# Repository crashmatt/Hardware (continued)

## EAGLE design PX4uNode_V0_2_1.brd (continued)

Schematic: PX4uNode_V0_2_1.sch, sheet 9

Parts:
D901: DIODE-SCHOTTKY; SOD-523; PARTNO MBRA140
D902, D903: B340A; SMA-DIODE; PARTNO B340A
D904: MSS1P4-M3; MICROSMP; PARTNO MSS1P4-M3/89A
JP901: M02PTH3; 1X02_LONGPADS
R901, R902, R903: 10K/0.1%; 0402-RES; PARTNO ERA-2AEB103X

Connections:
GND: D901.A, JP901.2, R903.P$1 (1); also elsewhere on the board
unnamed: D901.C, R901.P$1 (1), R902.P$2 (2)
VBUS: D904.ANODE (A); also elsewhere on the board
VDD_IN: D902.C, D903.C, D904.CATHODE (C); also elsewhere on the board
VDD_SERVO_SENSE: R902.P$1 (1), R903.P$2 (2); also elsewhere on the board
V_EXT: D903.A, JP901.1, R901.P$2 (2)
V_SERVO: D902.A; also elsewhere on the board

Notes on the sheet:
IO SoC Ports Spektrum/DSM port
Timer allocation: PA0: TIM2_CH1: IO-CH1 PA1: TIM2_CH2: IO-CH2 PB8: TIM4_CH3: IO-CH3 PB9: TIM4_CH4: IO-CH4 PA6: TIM3_CH1: IO-CH5 PA7: TIM3_CH2: IO-CH6 PB0: TIM3_CH3: IO-CH7 PB1: TIM3_CH4: IO-CH8 PA8: TIM1_CH1: PPM_IN PA11: TIM1_CH4: RSSI_IN

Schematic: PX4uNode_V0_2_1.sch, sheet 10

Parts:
J1001: SERVO_HEADER-3X8; 3X8RA_SERVO
JP1001, JP1002: M01SMD-4.5X1.5; PAD-1.5X4.5
L1001: NUF8402MN; DFN16-THIN; PARTNO NUF8402MN
R1001, R1002: 220R; 0402-RES; PARTNO RC0402FR-07220RL

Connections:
FMU-CH1: L1001.P$4; also elsewhere on the board
FMU-CH1-PROT: J1001.S1, L1001.P$9
FMU-CH2: L1001.P$5; also elsewhere on the board
FMU-CH3: L1001.P$6; also elsewhere on the board
FMU-CH4: L1001.P$7; also elsewhere on the board
FMU-CH5: L1001.P$2; also elsewhere on the board
FMU-CH6: L1001.P$3; also elsewhere on the board
FMU-CH7: L1001.P$8; also elsewhere on the board
FMU-CH8: L1001.P$1; also elsewhere on the board
FMU-CH9: R1001.P$2 (2); also elsewhere on the board
FMU-CH10: R1002.P$2 (2); also elsewhere on the board
GND: J1001.GND_S1, J1001.GND_S2, J1001.GND_S3, J1001.GND_S4, J1001.GND_S5, J1001.GND_S6, J1001.GND_S7, J1001.GND_S8, L1001.P$EP (GND); also elsewhere on the board
unnamed: J1001.S8, L1001.P$16
unnamed: J1001.S7, L1001.P$15
unnamed: JP1001.P$1, R1001.P$1 (1)
unnamed: JP1002.P$1, R1002.P$1 (1)
unnamed: J1001.S6, L1001.P$14
unnamed: J1001.S5, L1001.P$13
unnamed: J1001.S4, L1001.P$11
unnamed: J1001.S3, L1001.P$12
unnamed: J1001.S2, L1001.P$10
V_SERVO: J1001.PWR_S1, J1001.PWR_S2, J1001.PWR_S3, J1001.PWR_S4, J1001.PWR_S5, J1001.PWR_S6, J1001.PWR_S7, J1001.PWR_S8; also elsewhere on the board

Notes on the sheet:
Servo Header S.Bus interface
Servo outputs

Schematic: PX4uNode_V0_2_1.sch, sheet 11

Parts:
JP1101, JP1102, JP1103, JP1104: FIDUCIAL1.5X3; FIDUCIAL-1.5X3; PARTNO *
JP1105: M01PTH; 1X01
M3_MOUNT1101, M3_MOUNT1102, M3_MOUNT1103, M3_MOUNT1104: MOUNT-HOLE3.1MM; MOUNT-HOLE3.1; PARTNO *
OSHW_LOGO: OSHW-LOGOS; OSHW-LOGO-S; PARTNO *

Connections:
FMU-BOOT0: JP1105.1; also elsewhere on the board

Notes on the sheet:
Mounting holes to suit M3 fastener
and Richco R908 series spacer.
Use R908-5 spacers to stack with
other PX4 series boards (7.95 mm).
Production Testing Pads
Test and Fiducials
Minimum drill: 0.3 mm
Minimum trace width (use mm for traces): 0.15 mm
Minimum copper distance (all signals): 0.15 mm
Dimension / hole minimum distance: 0.2 mm
Layout grid: 4 mil, part grid: 4 mil. Dimensions / hole positions: 0.5 mm
Board: FR4 black, 1.0 mm. Solder stop on vias < 0.6 mm.
Signoff rules: Footprint checked, pinmap checked, schematic checked, cross-references to other pages checked.
Routing: 1: general/escape 2: ground 3: horizontal 4: vertical 5: power 6: general/escape
Fiducials for machine vision alignment.

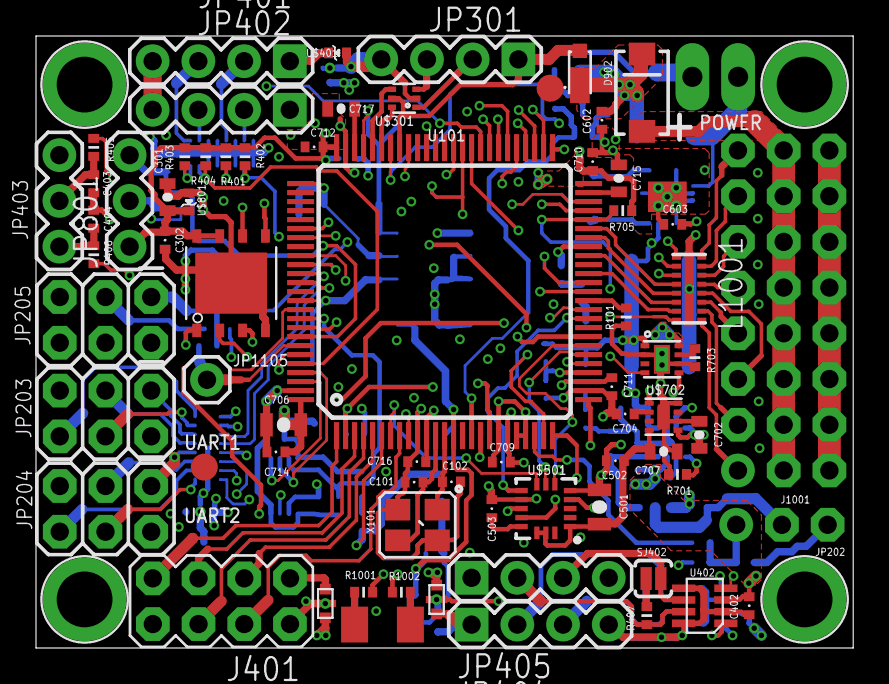
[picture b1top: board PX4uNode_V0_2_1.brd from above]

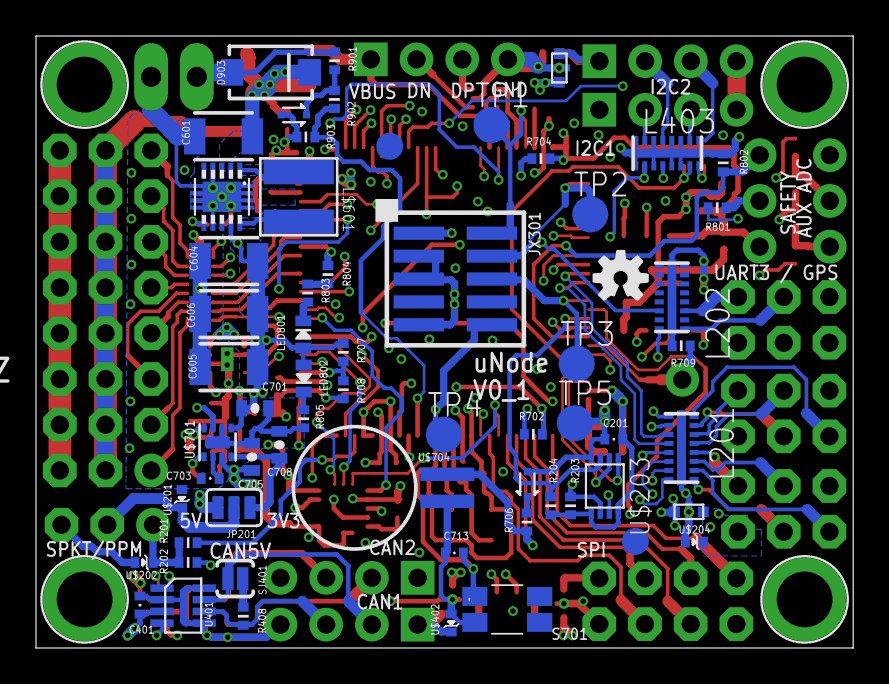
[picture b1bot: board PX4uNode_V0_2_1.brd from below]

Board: 6 copper layers, 45.4 x 34.0 mm, 138 parts (62 on the bottom side), 136 nets.

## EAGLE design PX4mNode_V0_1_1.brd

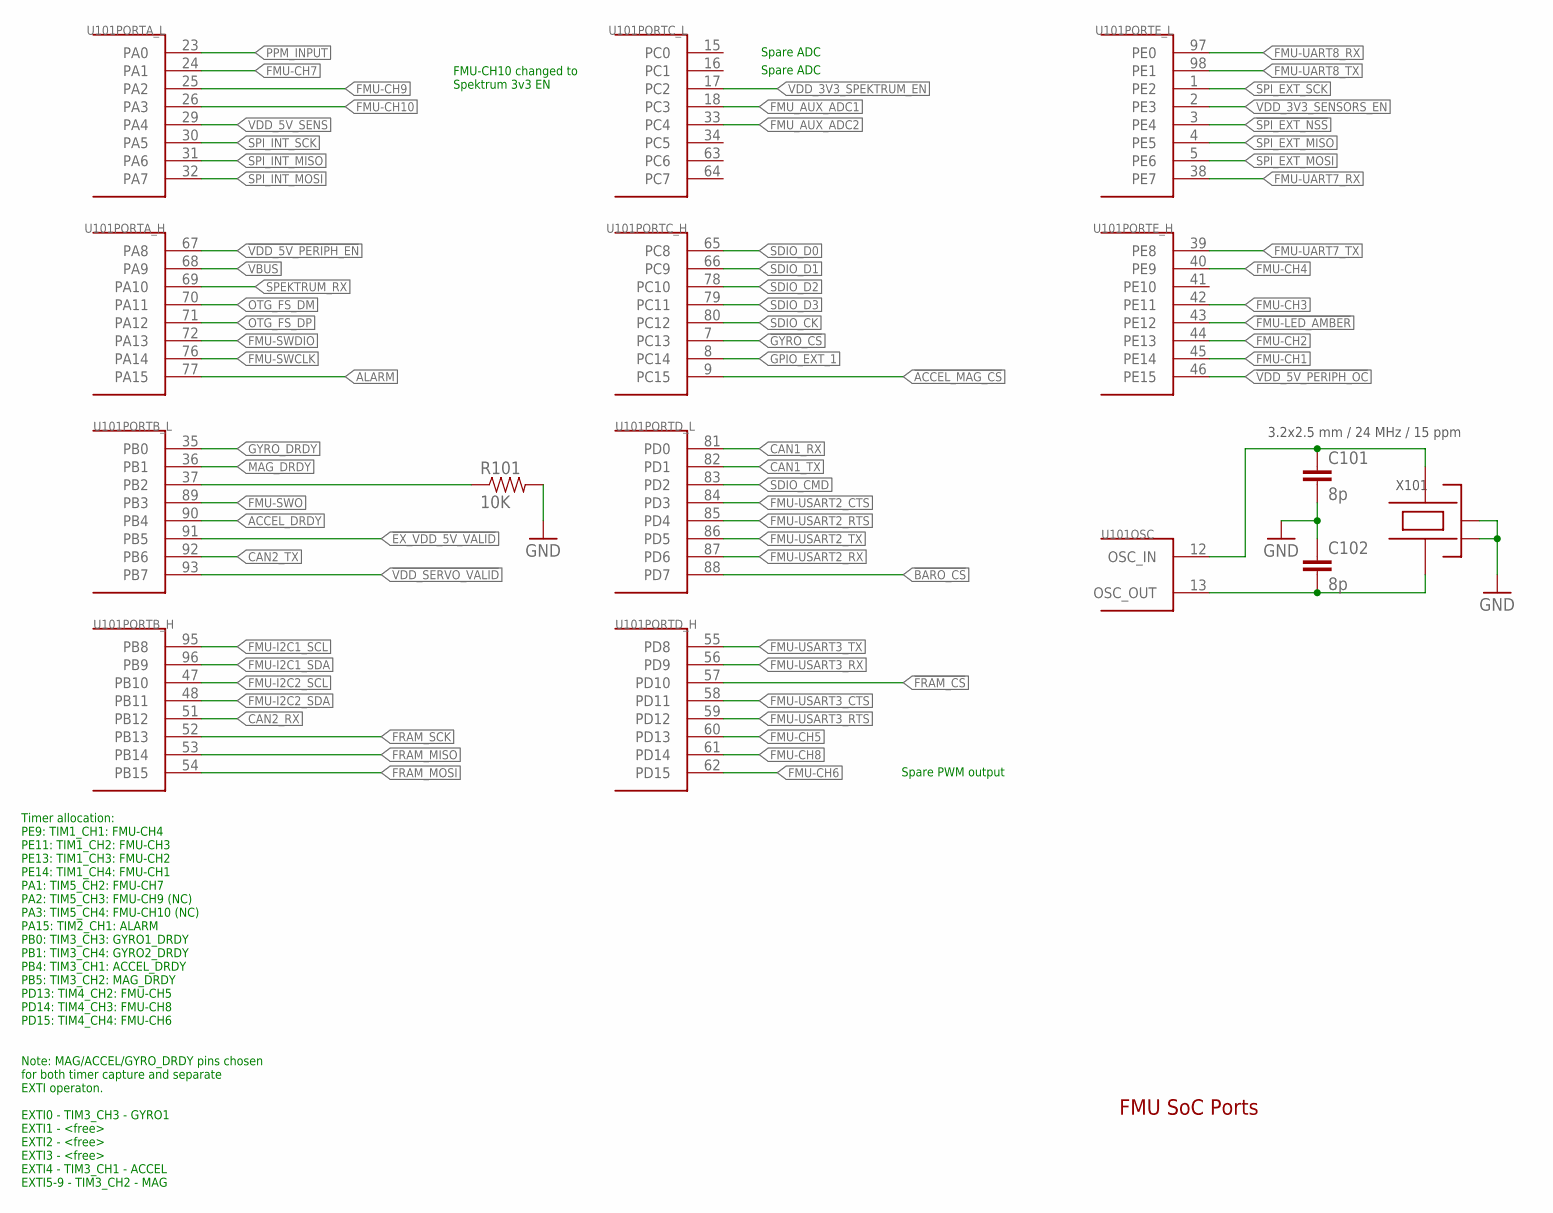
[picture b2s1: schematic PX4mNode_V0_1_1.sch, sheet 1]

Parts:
C101, C102: 8p; 0402-CAP; PARTNO C1005C0G1H080C
R101: 10K; 0402-RES; PARTNO RC0402FR-0710KL
U101: STM32F4X7VX; TQFP100; PARTNO STM32F427VI
X101: 3.2x2.5 mm / 24 MHz / 15 ppm; OSCILLATOR-3.2X2.5; PARTNO NX3225SA-24.000000MHZ

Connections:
!ACCEL_MAG_CS: U101.9 (PC15)
!BARO_CS: U101.88 (PD7)
!EX_VDD_5V_VALID: U101.91 (PB5)
!FMU-LED_AMBER: U101.43 (PE12); also elsewhere on the board
!FRAM_CS: U101.57 (PD10)
!GYRO_CS: U101.7 (PC13); also elsewhere on the board
!SPI_EXT_NSS: U101.3 (PE4); also elsewhere on the board
!VDD_5V_PERIPH_EN: U101.67 (PA8); also elsewhere on the board
!VDD_5V_PERIPH_OC: U101.46 (PE15); also elsewhere on the board
!VDD_SERVO_VALID: U101.93 (PB7)
ACCEL_DRDY: U101.90 (PB4); also elsewhere on the board
ALARM: U101.77 (PA15)
CAN1_RX: U101.81 (PD0); also elsewhere on the board
CAN1_TX: U101.82 (PD1); also elsewhere on the board
CAN2_RX: U101.51 (PB12); also elsewhere on the board
CAN2_TX: U101.92 (PB6); also elsewhere on the board
FMU-CH1: U101.45 (PE14); also elsewhere on the board
FMU-CH2: U101.44 (PE13); also elsewhere on the board
FMU-CH3: U101.42 (PE11); also elsewhere on the board
FMU-CH4: U101.40 (PE9); also elsewhere on the board
FMU-CH5: U101.60 (PD13); also elsewhere on the board
FMU-CH6: U101.62 (PD15); also elsewhere on the board
FMU-CH7: U101.24 (PA1); also elsewhere on the board
FMU-CH8: U101.61 (PD14); also elsewhere on the board
FMU-CH9: U101.25 (PA2); also elsewhere on the board
FMU-CH10: U101.26 (PA3); also elsewhere on the board
FMU-I2C1_SCL: U101.95 (PB8); also elsewhere on the board
FMU-I2C1_SDA: U101.96 (PB9); also elsewhere on the board
FMU-I2C2_SCL: U101.47 (PB10); also elsewhere on the board
FMU-I2C2_SDA: U101.48 (PB11); also elsewhere on the board
FMU-SWCLK: U101.76 (PA14); also elsewhere on the board
FMU-SWDIO: U101.72 (PA13); also elsewhere on the board
FMU-SWO: U101.89 (PB3); also elsewhere on the board
FMU-UART7_RX: U101.38 (PE7); also elsewhere on the board
FMU-UART7_TX: U101.39 (PE8); also elsewhere on the board
FMU-UART8_RX: U101.97 (PE0); also elsewhere on the board
FMU-UART8_TX: U101.98 (PE1); also elsewhere on the board
FMU-USART2_CTS: U101.84 (PD3); also elsewhere on the board
FMU-USART2_RTS: U101.85 (PD4); also elsewhere on the board
FMU-USART2_RX: U101.87 (PD6); also elsewhere on the board
FMU-USART2_TX: U101.86 (PD5); also elsewhere on the board
FMU-USART3_CTS: U101.58 (PD11); also elsewhere on the board
FMU-USART3_RTS: U101.59 (PD12); also elsewhere on the board
FMU-USART3_RX: U101.56 (PD9); also elsewhere on the board
FMU-USART3_TX: U101.55 (PD8); also elsewhere on the board
FMU_AUX_ADC1: U101.18 (PC3); also elsewhere on the board
FMU_AUX_ADC2: U101.33 (PC4); also elsewhere on the board
FRAM_MISO: U101.53 (PB14)
FRAM_MOSI: U101.54 (PB15)
FRAM_SCK: U101.52 (PB13)
GND: C101.P$2 (2), C102.P$1 (1), R101.P$2 (2), X101.2 (NC_2), X101.4 (NC_4); also elsewhere on the board
GPIO_EXT_1: U101.8 (PC14); also elsewhere on the board
GYRO_DRDY: U101.35 (PB0); also elsewhere on the board
MAG_DRDY: U101.36 (PB1); also elsewhere on the board
unnamed: C102.P$2 (2), U101.13 (OSC_OUT), X101.1
unnamed: C101.P$1 (1), U101.12 (OSC_IN), X101.3
OTG_FS_DM: U101.70 (PA11); also elsewhere on the board
OTG_FS_DP: U101.71 (PA12); also elsewhere on the board
PB2-BOOT1: R101.P$1 (1), U101.37 (PB2)
PPM_INPUT: U101.23 (PA0); also elsewhere on the board
SDIO_CK: U101.80 (PC12); also elsewhere on the board
SDIO_CMD: U101.83 (PD2); also elsewhere on the board
SDIO_D0: U101.65 (PC8); also elsewhere on the board
SDIO_D1: U101.66 (PC9); also elsewhere on the board
SDIO_D2: U101.78 (PC10); also elsewhere on the board
SDIO_D3: U101.79 (PC11); also elsewhere on the board
SPEKTRUM_RX: U101.69 (PA10); also elsewhere on the board
SPI_EXT_MISO: U101.4 (PE5); also elsewhere on the board
SPI_EXT_MOSI: U101.5 (PE6); also elsewhere on the board
SPI_EXT_SCK: U101.1 (PE2); also elsewhere on the board
SPI_INT_MISO: U101.31 (PA6); also elsewhere on the board
SPI_INT_MOSI: U101.32 (PA7); also elsewhere on the board
SPI_INT_SCK: U101.30 (PA5); also elsewhere on the board
VBUS: U101.68 (PA9); also elsewhere on the board
VDD_3V3_SENSORS_EN: U101.2 (PE3); also elsewhere on the board
VDD_3V3_SPEKTRUM_EN: U101.17 (PC2); also elsewhere on the board
VDD_5V_SENS: U101.29 (PA4); also elsewhere on the board

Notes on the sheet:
FMU SoC Ports
Note: MAG/ACCEL/GYRO_DRDY pins chosen for both timer capture and separate EXTI operaton. EXTI0 - TIM3_CH3 - GYRO1 EXTI1 - <free> EXTI2 - <free> EXTI3 - <free> EXTI4 - TIM3_CH1 - ACCEL EXTI5-9 - TIM3_CH2 - MAG
Timer allocation: PE9: TIM1_CH1: FMU-CH4 PE11: TIM1_CH2: FMU-CH3 PE13: TIM1_CH3: FMU-CH2 PE14: TIM1_CH4: FMU-CH1 PA1: TIM5_CH2: FMU-CH7 PA2: TIM5_CH3: FMU-CH9 (NC) PA3: TIM5_CH4: FMU-CH10 (NC) PA15: TIM2_CH1: ALARM PB0: TIM3_CH3: GYRO1_DRDY PB1: TIM3_CH4: GYRO2_DRDY PB4: TIM3_CH1: ACCEL_DRDY PB5: T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
Spare PWM output
Spare ADC
FMU-CH10 changed to Spektrum 3v3 EN

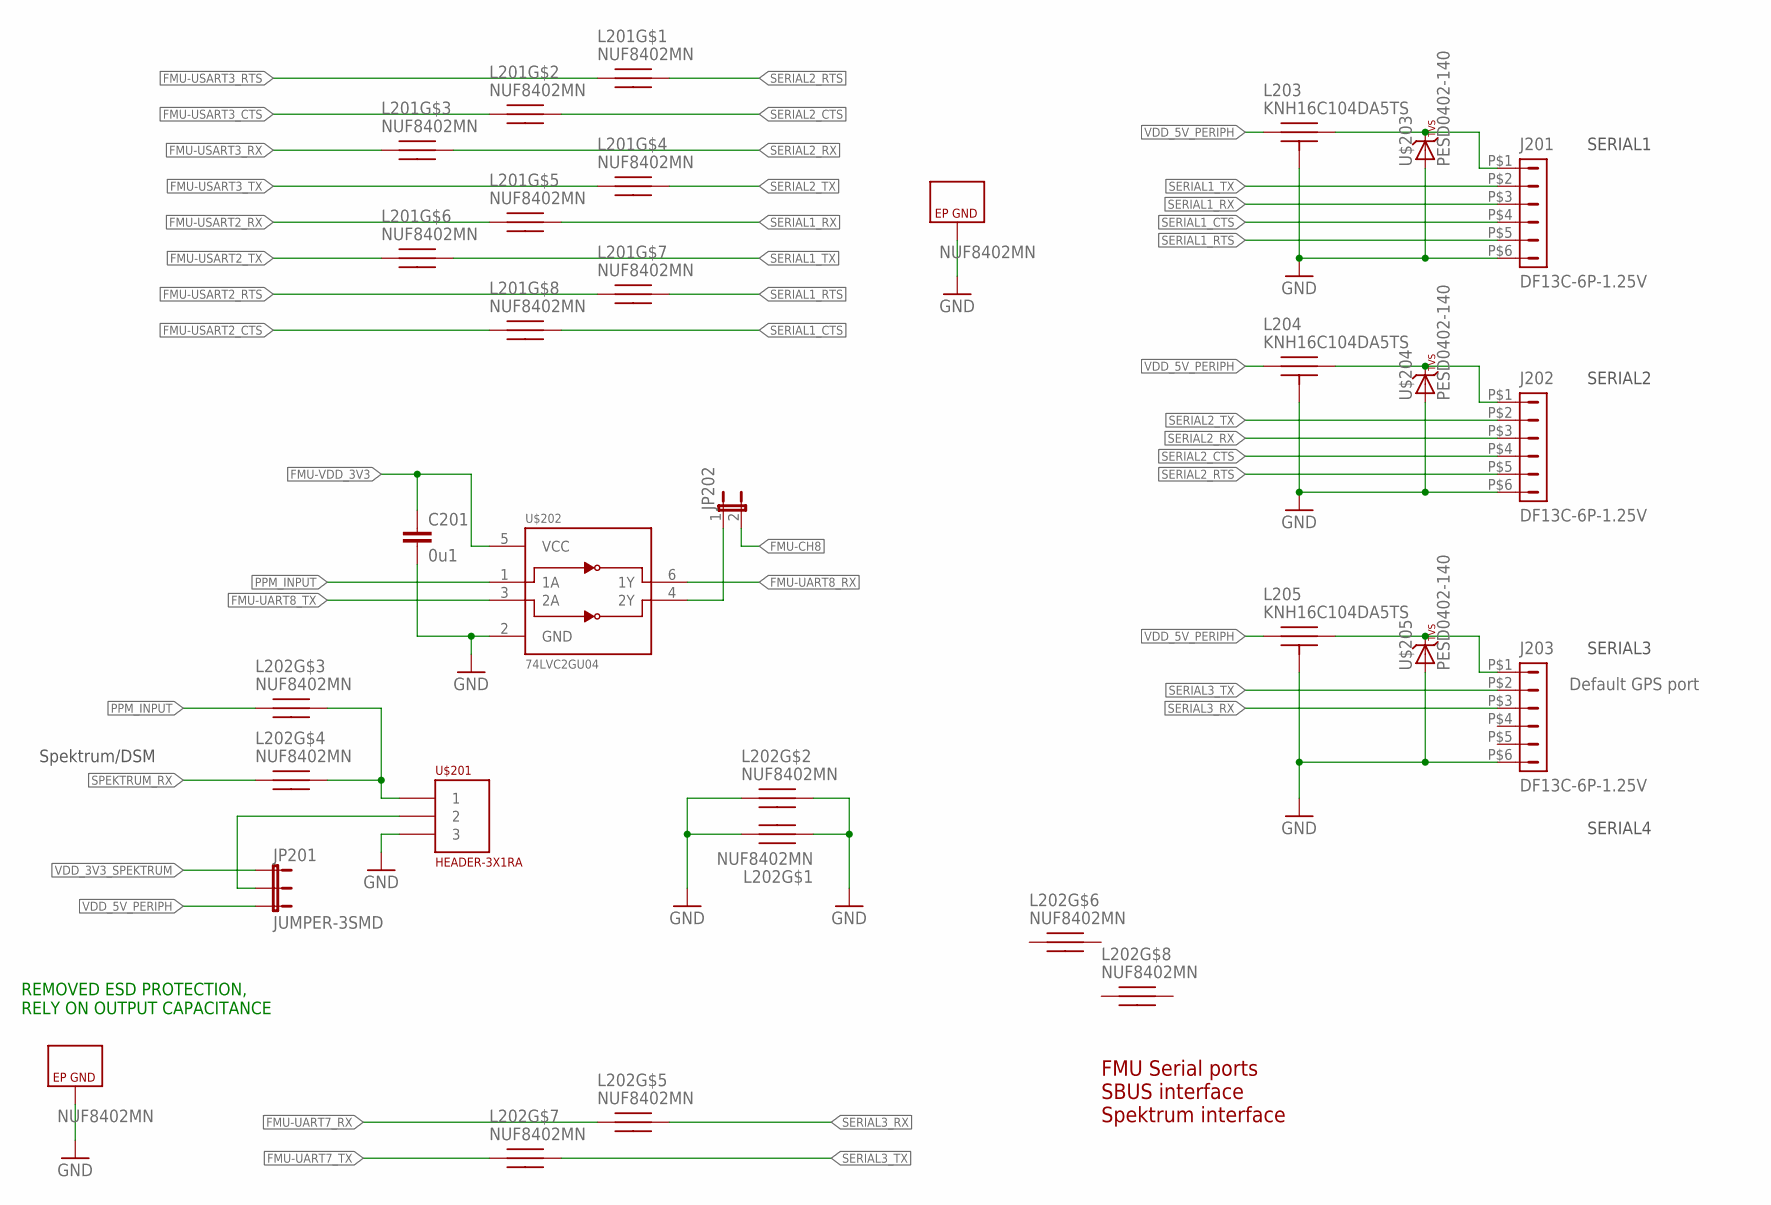
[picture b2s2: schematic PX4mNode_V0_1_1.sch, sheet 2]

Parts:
C201: 0u1; 0402-CAP; PARTNO CC0402ZRY5V7BB104
J201, J202, J203: DF13C-6P-1.25V; PARTNO DF13C-6P-1.25V(20)
JP201: JUMPER-3SMD; SJ_3
JP202: JUMPER-2SMD-NO; SJ_2S-NO
L201, L202: NUF8402MN; DFN16-THIN
L203, L204, L205: KNH16C104DA5TS; KYOCERA-KNH16-DA; PARTNO KNH16C104DA5TS
U$201: HEADER-3X1RA; 3X1RA
U$202: 74LVC2GU04; SOT363_PHILIPS; PARTNO 74LVC2GU04
U$203, U$204, U$205: PESD0402-140; 0402-TVS; PARTNO PESD0402-140

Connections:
5V_S1_FILTERED: J201.P$1 (1), L203.P$2, U$203.C
5V_S2_FILTERED: J202.P$1 (1), L204.P$2, U$204.C
5V_S3_FILTERED: J203.P$1 (1), L205.P$2, U$205.C
FMU-CH8: JP202.2; also elsewhere on the board
FMU-UART7_RX: L202.P$5; also elsewhere on the board
FMU-UART7_TX: L202.P$7; also elsewhere on the board
FMU-UART8_RX: U$202.6 (1Y); also elsewhere on the board
FMU-UART8_TX: U$202.3 (2A); also elsewhere on the board
FMU-USART2_CTS: L201.P$8; also elsewhere on the board
FMU-USART2_RTS: L201.P$7; also elsewhere on the board
FMU-USART2_RX: L201.P$5; also elsewhere on the board
FMU-USART2_TX: L201.P$6; also elsewhere on the board
FMU-USART3_CTS: L201.P$2; also elsewhere on the board
FMU-USART3_RTS: L201.P$1; also elsewhere on the board
FMU-USART3_RX: L201.P$3; also elsewhere on the board
FMU-USART3_TX: L201.P$4; also elsewhere on the board
FMU-VDD_3V3: C201.P$1 (1), U$202.5 (VCC); also elsewhere on the board
GND: C201.P$2 (2), J201.P$6 (6), J202.P$6 (6), J203.P$6 (6), L201.P$EP (GND), L202.P$1, L202.P$2, L202.P$15, L202.P$16, L202.P$EP (GND), L203.P$3, L203.P$4, L203.P$5, L204.P$3, L204.P$4, L204.P$5, L205.P$3, L205.P$4, L205.P$5, U$201.3, U$202.2 (GND), U$203.A, U$204.A, U$205.A; also elsewhere on the board
unnamed: JP202.1, U$202.4 (2Y)
unnamed: L202.P$13, L202.P$14, U$201.1
PPM_INPUT: L202.P$3, U$202.1 (1A); also elsewhere on the board
SERIAL1_CTS: J201.P$4 (4), L201.P$9
SERIAL1_RTS: J201.P$5 (5), L201.P$10
SERIAL1_RX: J201.P$3 (3), L201.P$12
SERIAL1_TX: J201.P$2 (2), L201.P$11
SERIAL2_CTS: J202.P$4 (4), L201.P$15
SERIAL2_RTS: J202.P$5 (5), L201.P$16
SERIAL2_RX: J202.P$3 (3), L201.P$14
SERIAL2_TX: J202.P$2 (2), L201.P$13
SERIAL3_RX: J203.P$3 (3), L202.P$12
SERIAL3_TX: J203.P$2 (2), L202.P$10
SPEKTRUM_RX: L202.P$4; also elsewhere on the board
VDD_3V3_SPEKTRUM: JP201.1; also elsewhere on the board
VDD_5V_PERIPH: JP201.3, L203.P$1, L204.P$1, L205.P$1; also elsewhere on the board
VDD_RX_POWER: JP201.2, U$201.2

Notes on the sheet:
FMU Serial ports SBUS interface Spektrum interface
SERIAL2
SERIAL1
SERIAL3
SERIAL4
Default GPS port
Spektrum/DSM
REMOVED ESD PROTECTION, RELY ON OUTPUT CAPACITANCE

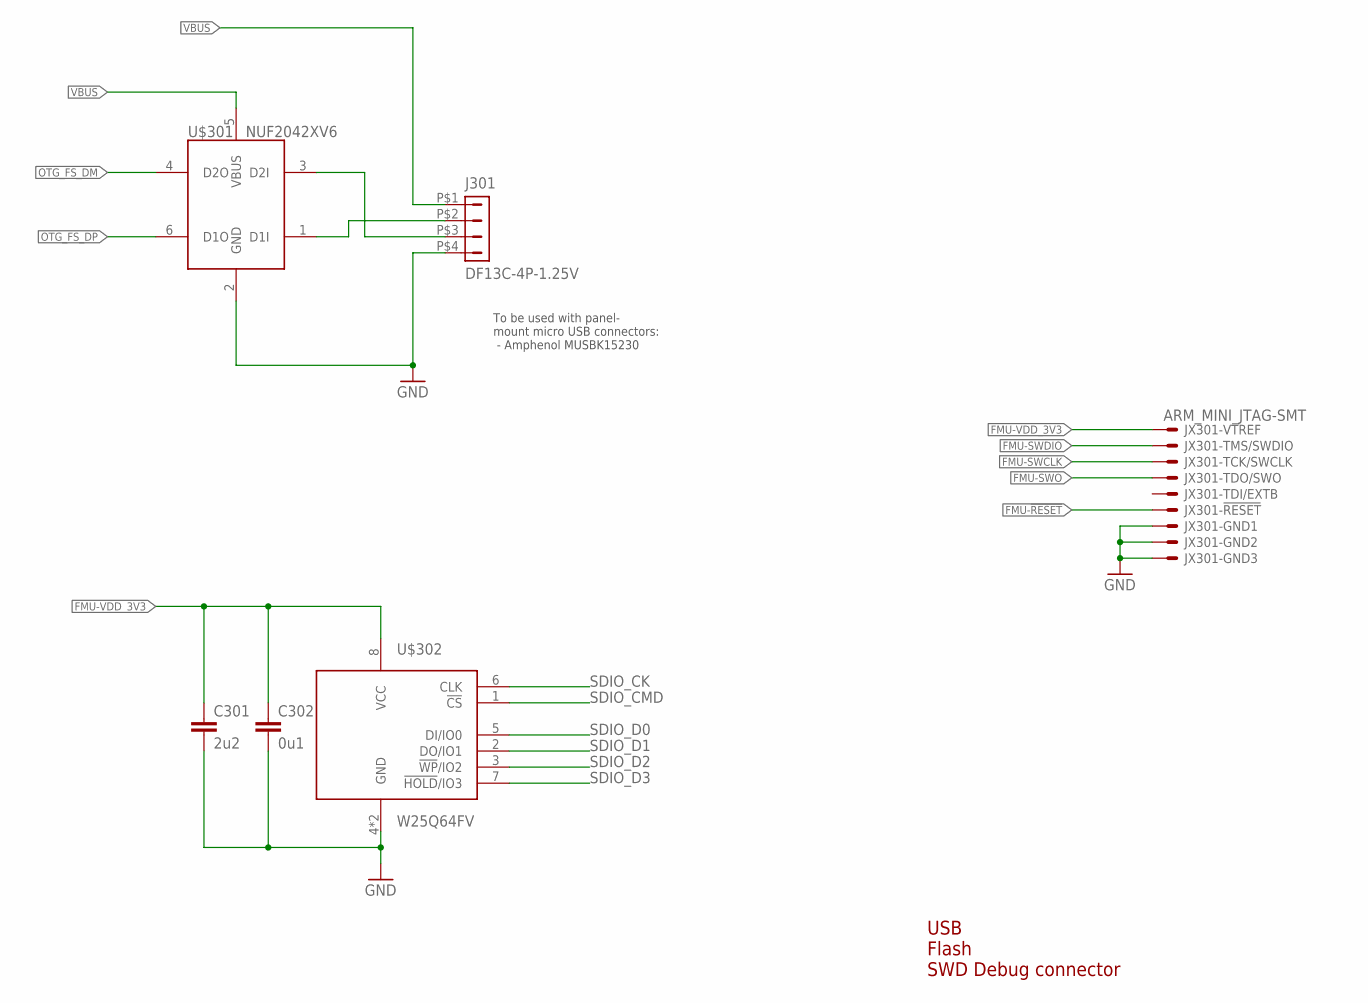
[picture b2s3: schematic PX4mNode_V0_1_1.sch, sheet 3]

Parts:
C301: 2u2; 0603-CAP; PARTNO C1608Y5V1C225Z
C302: 0u1; 0402-CAP; PARTNO CC0402ZRY5V7BB104
J301: DF13C-4P-1.25V; PARTNO DF13C-4P-1.25V(20)
JX301: ARM_MINI_JTAG-SMT; FTSH-105-01-XXX-DV-K; PARTNO M50-3900542
U$301: NUF2042XV6; SOT563-6
U$302: W25Q64FV; WSON-8-5X6

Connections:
FMU-!RESET: JX301.10; also elsewhere on the board
FMU-SWCLK: JX301.4; also elsewhere on the board
FMU-SWDIO: JX301.2; also elsewhere on the board
FMU-SWO: JX301.6; also elsewhere on the board
FMU-VDD_3V3: C301.P$1 (1), C302.P$1 (1), JX301.1, U$302.8 (VCC); also elsewhere on the board
GND: C301.P$2 (2), C302.P$2 (2), J301.P$4 (4), JX301.3, JX301.5, JX301.9, U$301.2 (GND), U$302.4 (GND), U$302.PAD (GND); also elsewhere on the board
OTG_DM1: J301.P$3 (3), U$301.3 (D2I)
OTG_DP1: J301.P$2 (2), U$301.1 (D1I)
OTG_FS_DM: U$301.4 (D2O); also elsewhere on the board
OTG_FS_DP: U$301.6 (D1O); also elsewhere on the board
SDIO_CK: U$302.6 (CLK); also elsewhere on the board
SDIO_CMD: U$302.1 (!CS); also elsewhere on the board
SDIO_D0: U$302.5 (DI/IO0); also elsewhere on the board
SDIO_D1: U$302.2 (DO/IO1); also elsewhere on the board
SDIO_D2: U$302.3 (!WP!/IO2); also elsewhere on the board
SDIO_D3: U$302.7 (!HOLD!/IO3); also elsewhere on the board
VBUS: J301.P$1 (1), U$301.5 (VBUS); also elsewhere on the board

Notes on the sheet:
USB Flash SWD Debug connector
To be used with panel- mount micro USB connectors: - Amphenol MUSBK15230

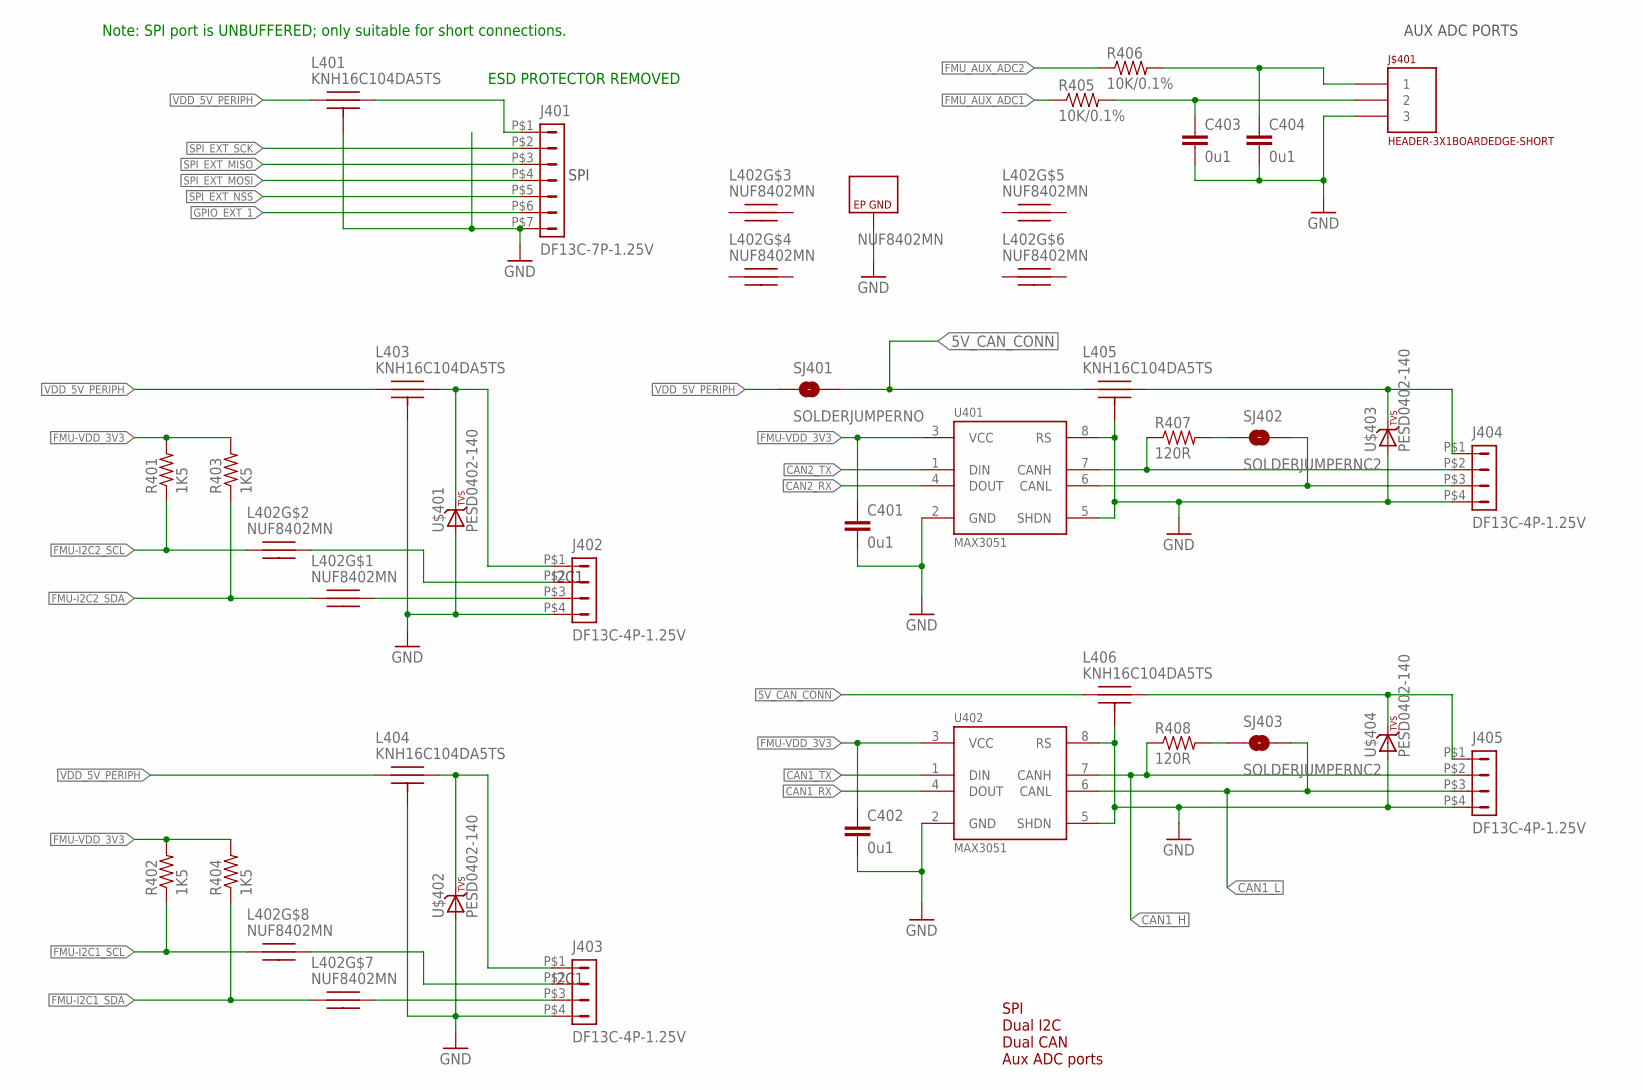
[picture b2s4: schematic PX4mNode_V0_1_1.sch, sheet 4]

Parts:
C401, C402, C403, C404: 0u1; 0402-CAP; PARTNO CC0402ZRY5V7BB104
J401: DF13C-7P-1.25V; PARTNO DF13C-7P-1.25V(20)
J402, J403, J404, J405: DF13C-4P-1.25V; PARTNO DF13C-4P-1.25V(20)
J$401: HEADER-3X1BOARDEDGE-SHORT; HEADER_3X01_SMD_H_BOARD_EDGE_SHORT
L401, L403, L404, L405, L406: KNH16C104DA5TS; KYOCERA-KNH16-DA; PARTNO KNH16C104DA5TS
L402: NUF8402MN; DFN16-THIN
R401, R402, R403, R404: 1K5; 0402-RES; PARTNO RC0402FR-071K5L
R405, R406: 10K/0.1%; 0402-RES; PARTNO ERA-2AEB103X
R407, R408: 120R; 0402-RES; PARTNO RC0402FR-07120RL
SJ401: SOLDERJUMPERNO; SJ_2S-NO
SJ402, SJ403: SOLDERJUMPERNC2; SJ_2S-NOTRACE
U401, U402: MAX3051; SOT23-8; PARTNO MAX3051EKA
U$401, U$402, U$403, U$404: PESD0402-140; 0402-TVS; PARTNO PESD0402-140

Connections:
5V_CAN_CONN: L405.P$1, L406.P$1, SJ401.2
!SPI_EXT_NSS: J401.P$5 (5); also elsewhere on the board
CAN1_H: J405.P$2 (2), R408.P$1 (1), U402.7 (CANH)
CAN1_L: J405.P$3 (3), SJ403.2, U402.6 (CANL)
CAN1_RX: U402.4 (DOUT); also elsewhere on the board
CAN1_TX: U402.1 (DIN); also elsewhere on the board
CAN2_H: J404.P$2 (2), R407.P$1 (1), U401.7 (CANH)
CAN2_L: J404.P$3 (3), SJ402.2, U401.6 (CANL)
CAN2_RX: U401.4 (DOUT); also elsewhere on the board
CAN2_TX: U401.1 (DIN); also elsewhere on the board
FMU-I2C1_SCL: L402.P$8, R402.P$1 (1); also elsewhere on the board
FMU-I2C1_SDA: L402.P$7, R404.P$1 (1); also elsewhere on the board
FMU-I2C2_SCL: L402.P$2, R401.P$1 (1); also elsewhere on the board
FMU-I2C2_SDA: L402.P$1, R403.P$1 (1); also elsewhere on the board
FMU-VDD_3V3: C401.P$1 (1), C402.P$1 (1), R401.P$2 (2), R402.P$2 (2), R403.P$2 (2), R404.P$2 (2), U401.3 (VCC), U402.3 (VCC); also elsewhere on the board
FMU_AUX_ADC1: R405.P$1 (1); also elsewhere on the board
FMU_AUX_ADC1_PROT: C403.P$1 (1), J$401.2, R405.P$2 (2)
FMU_AUX_ADC2: R406.P$1 (1); also elsewhere on the board
FMU_AUX_ADC2_PROT: C404.P$1 (1), J$401.1, R406.P$2 (2)
GND: C401.P$2 (2), C402.P$2 (2), C403.P$2 (2), C404.P$2 (2), J401.P$7 (7), J402.P$4 (4), J403.P$4 (4), J404.P$4 (4), J405.P$4 (4), J$401.3, L401.P$3, L401.P$4, L401.P$5, L402.P$EP (GND), L403.P$3, L403.P$4, L403.P$5, L404.P$3, L404.P$4, L404.P$5, L405.P$3, L405.P$4, L405.P$5, L406.P$3, L406.P$4, L406.P$5, U401.2 (GND), U401.5 (SHDN), U401.8 (RS), U402.2 (GND), U402.5 (SHDN), U402.8 (RS), U$401.A, U$402.A, U$403.A, U$404.A; also elsewhere on the board
GPIO_EXT_1: J401.P$6 (6); also elsewhere on the board
unnamed: J402.P$2 (2), L402.P$15
unnamed: J402.P$3 (3), L402.P$16
unnamed: J402.P$1 (1), L403.P$2, U$401.C
unnamed: R408.P$2 (2), SJ403.1
unnamed: J404.P$1 (1), L405.P$2, U$403.C
unnamed: R407.P$2 (2), SJ402.1
unnamed: J403.P$2 (2), L402.P$9
unnamed: J403.P$3 (3), L402.P$10
unnamed: J401.P$1 (1), L401.P$2
unnamed: J403.P$1 (1), L404.P$2, U$402.C
unnamed: J405.P$1 (1), L406.P$2, U$404.C
SPI_EXT_MISO: J401.P$3 (3); also elsewhere on the board
SPI_EXT_MOSI: J401.P$4 (4); also elsewhere on the board
SPI_EXT_SCK: J401.P$2 (2); also elsewhere on the board
VDD_5V_PERIPH: L401.P$1, L403.P$1, L404.P$1, SJ401.1; also elsewhere on the board

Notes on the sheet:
SPI
I2C1
AUX ADC PORTS
SPI Dual I2C Dual CAN Aux ADC ports
Note: SPI port is UNBUFFERED; only suitable for short connections.
ESD PROTECTOR REMOVED

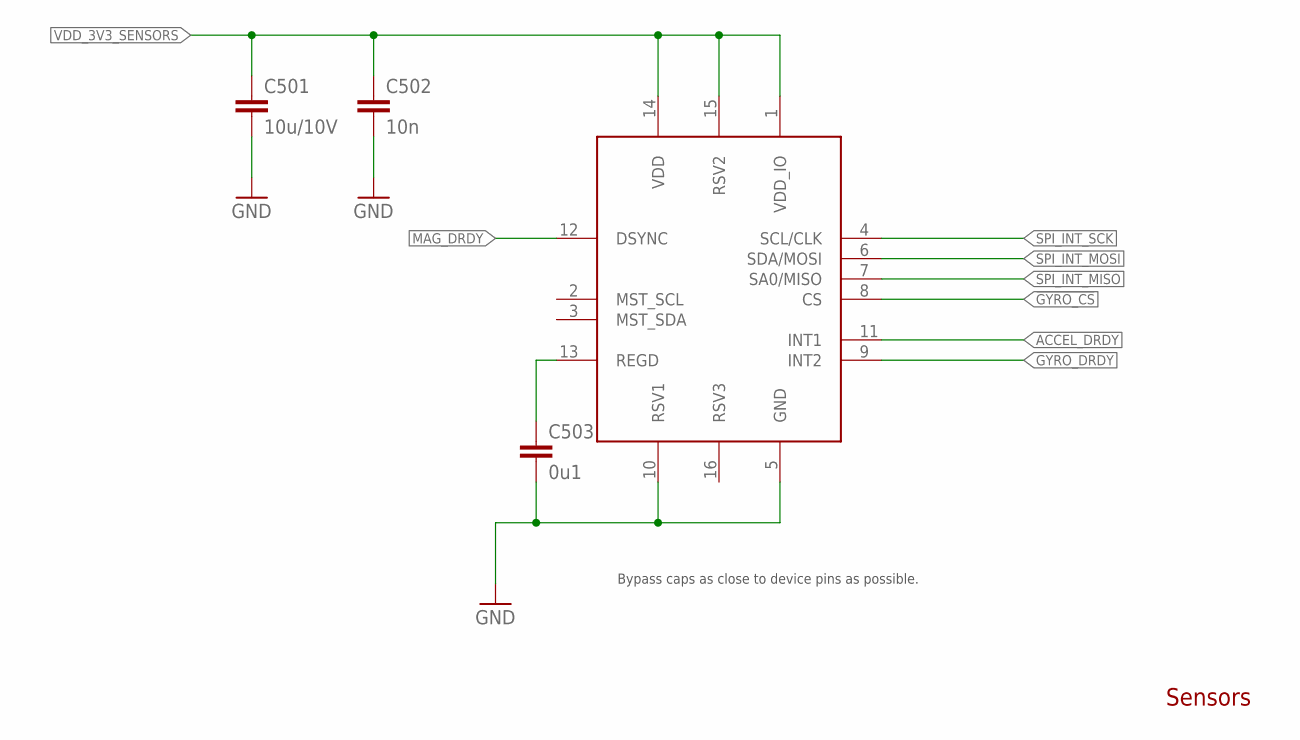
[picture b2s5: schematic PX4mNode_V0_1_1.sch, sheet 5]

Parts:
C501: 10u/10V; 0805-CAP; PARTNO CC0805ZKY5V6BB106
C502: 10n; 0402-CAP; PARTNO CC0402KRX7R7BB103
C503: 0u1; 0402-CAP; PARTNO CC0402ZRY5V7BB104
U$501: MAX21100; 16LGA-3X3

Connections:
!GYRO_CS: U$501.8 (CS); also elsewhere on the board
ACCEL_DRDY: U$501.11 (INT1); also elsewhere on the board
GND: C501.P$2 (2), C502.P$2 (2), C503.P$2 (2), U$501.5 (GND), U$501.10 (RSV1); also elsewhere on the board
GYRO_DRDY: U$501.9 (INT2); also elsewhere on the board
MAG_DRDY: U$501.12 (DSYNC); also elsewhere on the board
REGD: C503.P$1 (1), U$501.13 (REGD)
SPI_INT_MISO: U$501.7 (SA0/MISO); also elsewhere on the board
SPI_INT_MOSI: U$501.6 (SDA/MOSI); also elsewhere on the board
SPI_INT_SCK: U$501.4 (SCL/CLK); also elsewhere on the board
VDD_3V3_SENSORS: C501.P$1 (1), C502.P$1 (1), U$501.1 (VDD_IO), U$501.14 (VDD), U$501.15 (RSV2); also elsewhere on the board

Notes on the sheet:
Sensors
Bypass caps as close to device pins as possible.

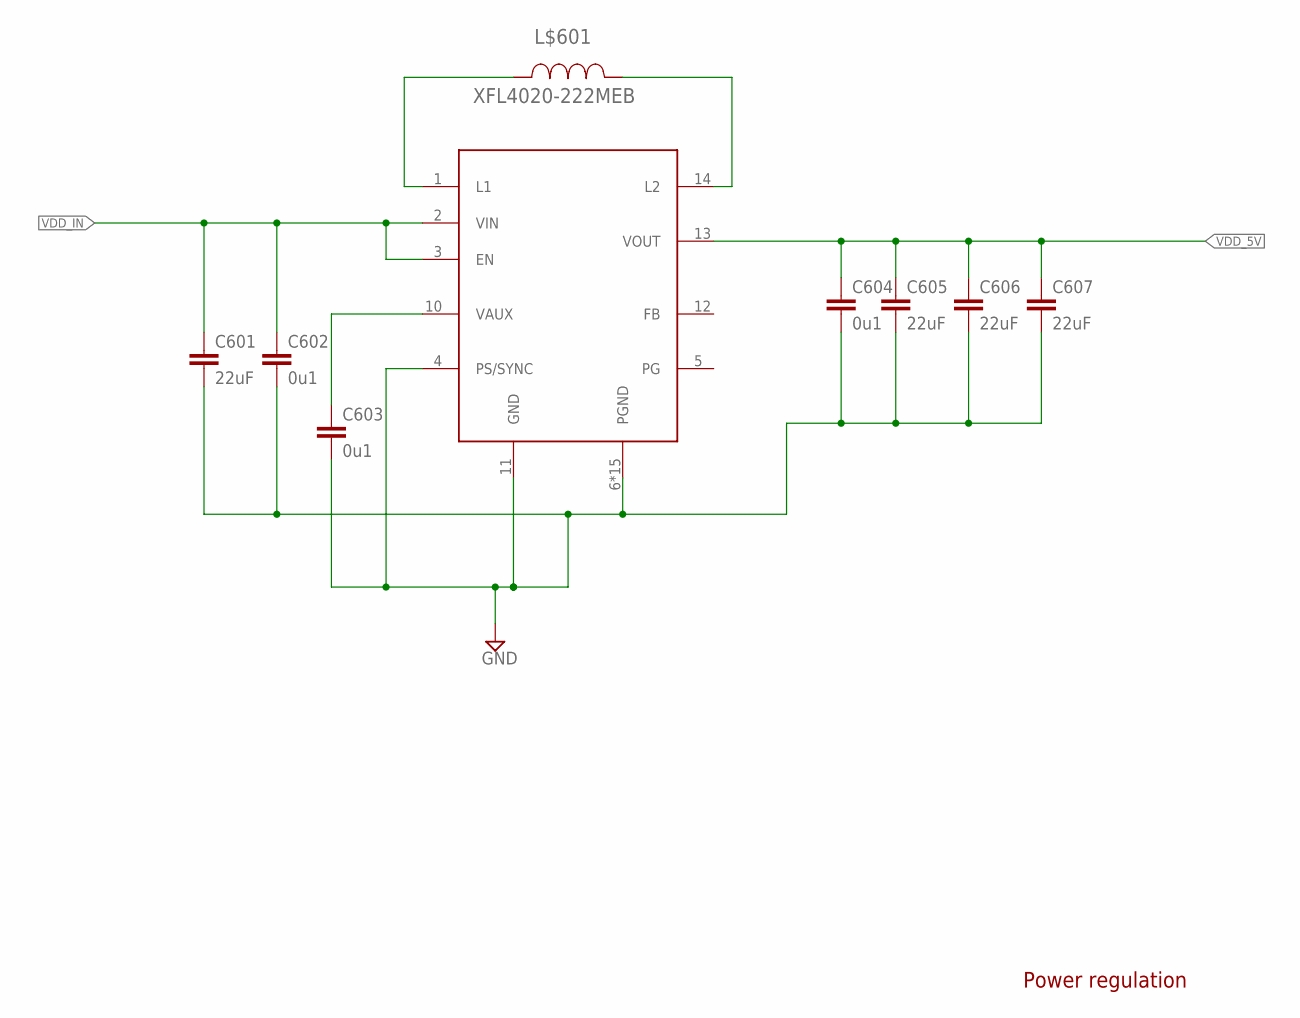
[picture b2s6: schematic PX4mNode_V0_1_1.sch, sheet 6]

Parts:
C601, C605, C606, C607: 22uF; 1210
C602, C603, C604: 0u1; 0402-CAP; PARTNO CC0402ZRY5V7BB104
L$601: XFL4020-222MEB; XFL4020
U$601: TPS6303X; PWSON10

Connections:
GND: C601.2, C602.P$2 (2), C603.P$2 (2), C604.P$2 (2), C605.2, C606.2, C607.2, U$601.4 (PS/SYNC), U$601.6 (PGND), U$601.7 (PGND), U$601.8 (PGND), U$601.9 (PGND), U$601.11 (GND), U$601.15 (PGND), U$601.16 (PGND), U$601.17 (PGND), U$601.18 (PGND), U$601.19 (PGND), U$601.20 (PGND), U$601.21 (PGND), U$601.22 (PGND), U$601.23 (PGND), U$601.EP (PGND), U$601.EP1 (PGND); also elsewhere on the board
unnamed: L$601.1, U$601.14 (L2)
unnamed: L$601.2, U$601.1 (L1)
unnamed: C603.P$1 (1), U$601.10 (VAUX)
VDD_5V: C604.P$1 (1), C605.1, C606.1, C607.1, U$601.13 (VOUT); also elsewhere on the board
VDD_IN: C601.1, C602.P$1 (1), U$601.2 (VIN), U$601.3 (EN); also elsewhere on the board

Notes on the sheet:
Power regulation
